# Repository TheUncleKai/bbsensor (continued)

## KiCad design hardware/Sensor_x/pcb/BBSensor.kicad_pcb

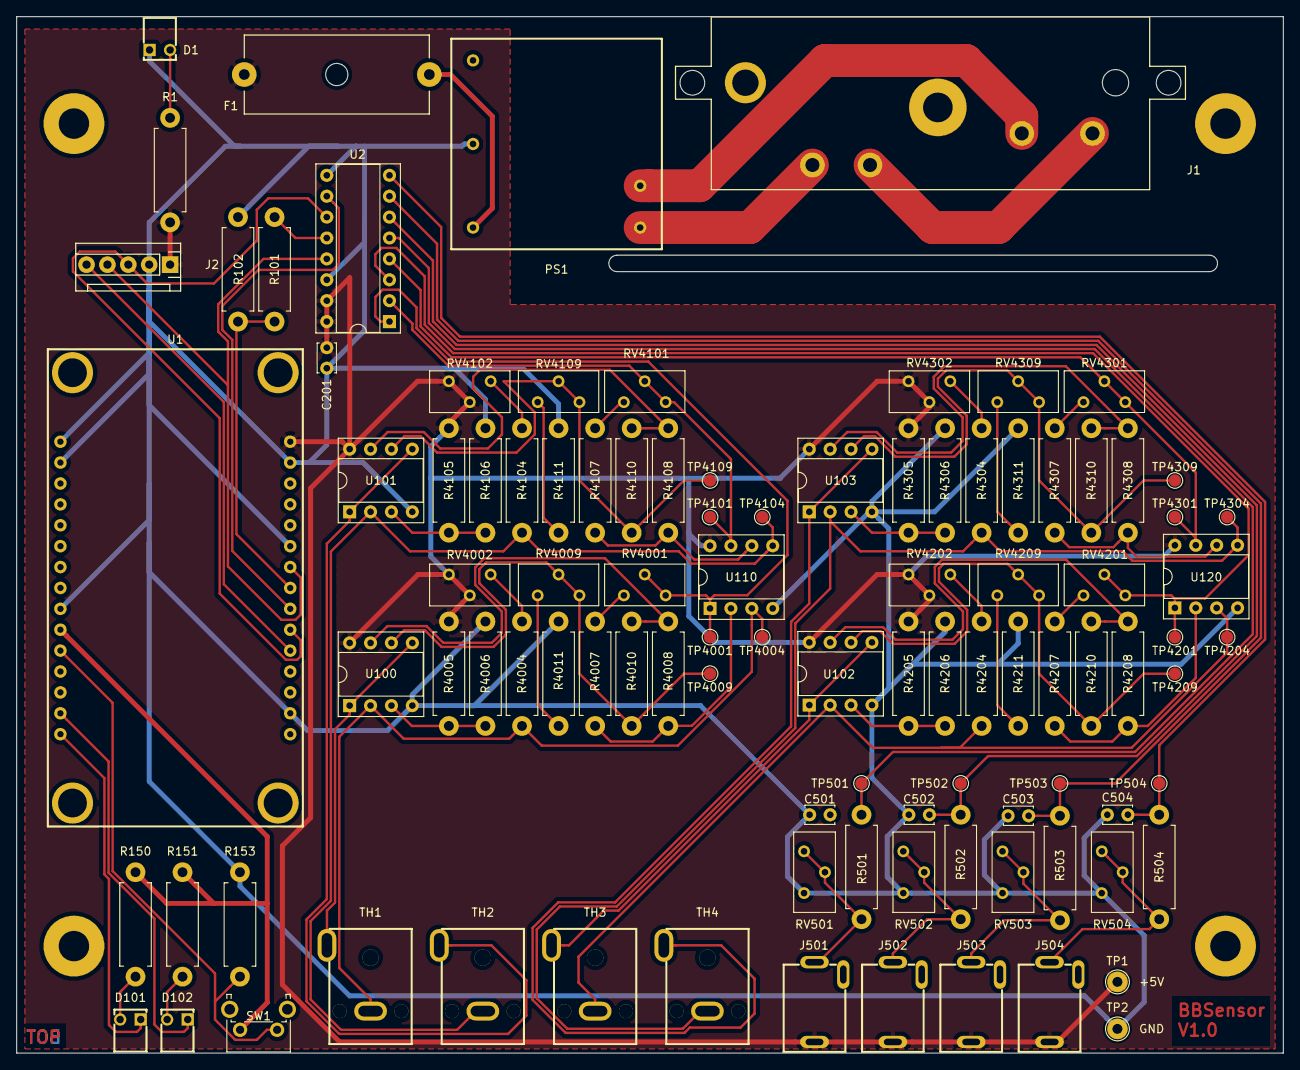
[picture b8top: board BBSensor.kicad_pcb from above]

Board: 2 copper layers, 154.0 x 126.0 mm, 101 parts (0 on the bottom side), 67 nets.

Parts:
C201, C501, C502, C503, C504: 100n; C_Disc_D3.4mm_W2.1mm_P2.50mm
D1: POWER; 5600F
D101: RED; 5600F
D102: GREEN; 5600F
F1: Fuse; Fuse_holder_20x5_22.5
J1: Schurter_CMF1; CMF1
J2: Display; Molex_KK256_Pin_Header_Straight_1x05
J501, J502, J503, J504: AudioJack2_SwitchT; LUMBERG_1501_09
PS1: TMPS_05; Traco_TMPS_05
R1: 220; R_Axial_DIN0411_L9.9mm_D3.6mm_P12.70mm_Horizontal
R101: 1k; R_Axial_DIN0411_L9.9mm_D3.6mm_P12.70mm_Horizontal
R102, R153, R4004, R4104, R4204, R4304: 2k2; R_Axial_DIN0411_L9.9mm_D3.6mm_P12.70mm_Horizontal
R150, R151: 140; R_Axial_DIN0411_L9.9mm_D3.6mm_P12.70mm_Horizontal
R501, R502, R503, R504, R4005, R4006, R4105, R4106, R4205, R4206, R4305, R4306: 10k; R_Axial_DIN0411_L9.9mm_D3.6mm_P12.70mm_Horizontal
R4007, R4107, R4207, R4307: 4k7; R_Axial_DIN0411_L9.9mm_D3.6mm_P12.70mm_Horizontal
R4008, R4010, R4108, R4110, R4208, R4210, R4308, R4310: 200; R_Axial_DIN0411_L9.9mm_D3.6mm_P12.70mm_Horizontal
R4011, R4111, R4211, R4311: 2k; R_Axial_DIN0411_L9.9mm_D3.6mm_P12.70mm_Horizontal
RV501, RV502, RV503, RV504: 10k; Potentiometer_Bourns_3296Y_Vertical
RV4001, RV4101, RV4201, RV4301: 405; Potentiometer_Bourns_3296Y_Vertical
RV4002, RV4102, RV4202, RV4302: 300; Potentiometer_Bourns_3296Y_Vertical
RV4009, RV4109, RV4209, RV4309: 470; Potentiometer_Bourns_3296Y_Vertical
SW1: SW_Push; SW_Tactile_SPST_Angled_PTS645Vx83-2LFS
TH1, TH2, TH3, TH4: Thermistor_NTC; LUMBERG_1553_02
TP1, TP2: TestPoint; TestPoint_THTPad_D2.5mm_Drill1.2mm
TP501, TP502, TP503, TP504, TP4001, TP4004, TP4009, TP4101, TP4104, TP4109, TP4201, TP4204, TP4209, TP4301, TP4304, TP4309: TestPoint; TestPoint_Pad_D1.5mm
U1: ESP8266-12E_NodeMCU_Lolin
U2: MCP3208; DIP-16_W7.62mm_Socket
U100, U101, U102, U103, U110, U120: OPA2340; DIP-8_W7.62mm_Socket

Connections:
+3V3: R150.1, R151.1, SW1.2, U1.21
+5V: C201.1, F1.1, J2.1, J501.S, J502.S, J503.S, J504.S, R1.2, R4005.2, R4105.2, R4205.2, R4305.2, RV4002.2, RV4002.3, RV4102.2, RV4102.3, RV4202.2, RV4202.3, RV4302.2, RV4302.3, TP1.1, U1.15, U2.15, U2.16, U100.8, U101.8, U102.8, U103.8, U110.8, U120.8
/Analog/Digital/SPI1: J2.3, U1.6, U2.11
/Analog/Digital/SPI2: R101.2, U2.12
/Analog/Digital/SPI3: J2.4, U1.9, U2.13
/Analog/Digital/SPI4: U1.7, U2.10
/Analog/Digital/TEMP1: RV4001.2, RV4001.3, TP4001.1, U2.1, U110.1
/Analog/Digital/TEMP2: RV4101.2, RV4101.3, TP4101.1, U2.2, U110.7
/Analog/Digital/TEMP3: RV4201.2, RV4201.3, TP4201.1, U2.3, U120.1
/Analog/Digital/TEMP4: RV4301.2, RV4301.3, TP4301.1, U2.4, U120.7
/Analog/Digital/TEMP5: C501.1, R501.1, TP501.1, U2.5
/Analog/Digital/TEMP6: C502.1, R502.1, TP502.1, U2.6
/Analog/Digital/TEMP7: C503.1, R503.1, TP503.1, U2.7
/Analog/Digital/TEMP8: C504.1, R504.1, TP504.1, U2.8
/Display/SPI5: J2.5, U1.5
/ESP8266/MISO: R101.1, R102.1, U1.8
GND: C201.2, C501.2, C502.2, C503.2, C504.2, D1.1, J2.2, PS1.4, R102.2, R153.2, R4006.1, R4011.2, R4106.1, R4111.2, R4206.1, R4211.2, R4306.1, R4311.2, RV501.3, RV502.3, RV503.3, RV504.3, TP2.1, U1.2, U1.10, U1.14, U1.22, U1.29, U1.30, U2.9, U2.14, U100.4, U101.4, U102.4, U103.4, U110.4, U120.4
unnamed: D1.2, R1.1
unnamed: D101.1, U1.16
unnamed: D101.2, R150.2
unnamed: D102.1, U1.17
unnamed: D102.2, R151.2
unnamed: F1.2, PS1.5
unnamed: J1.1, PS1.2
unnamed: J1.2, J1.4
unnamed: J1.3, PS1.1
unnamed: J501.T, R501.2, RV501.1, RV501.2
unnamed: J502.T, R502.2, RV502.1, RV502.2
unnamed: J503.T, R503.2, RV503.1, RV503.2
unnamed: J504.T, R504.2, RV504.1, RV504.2
unnamed: R153.1, SW1.1, U1.20
unnamed: R4004.1, TH1.2, TP4004.1, U100.2, U110.3
unnamed: R4004.2, RV4002.1
unnamed: R4005.1, R4006.2, U100.3
unnamed: R4007.1, RV4001.1
unnamed: R4007.2, R4008.1, U110.2
unnamed: R4008.2, R4010.1, U100.7
unnamed: R4010.2, RV4009.2, RV4009.3, TP4009.1, U100.6
unnamed: R4011.1, RV4009.1
unnamed: R4104.1, TH2.2, TP4104.1, U101.2, U110.5
unnamed: R4104.2, RV4102.1
unnamed: R4105.1, R4106.2, U101.3
unnamed: R4107.1, RV4101.1
unnamed: R4107.2, R4108.1, U110.6
unnamed: R4108.2, R4110.1, U101.7
unnamed: R4110.2, RV4109.2, RV4109.3, TP4109.1, U101.6
unnamed: R4111.1, RV4109.1
unnamed: R4204.1, TH3.2, TP4204.1, U102.2, U120.3
unnamed: R4204.2, RV4202.1
unnamed: R4205.1, R4206.2, U102.3
unnamed: R4207.1, RV4201.1
unnamed: R4207.2, R4208.1, U120.2
unnamed: R4208.2, R4210.1, U102.7
unnamed: R4210.2, RV4209.2, RV4209.3, TP4209.1, U102.6
unnamed: R4211.1, RV4209.1
unnamed: R4304.1, TH4.2, TP4304.1, U103.2, U120.5
unnamed: R4304.2, RV4302.1
unnamed: R4305.1, R4306.2, U103.3
unnamed: R4307.1, RV4301.1
unnamed: R4307.2, R4308.1, U120.6
unnamed: R4308.2, R4310.1, U103.7
unnamed: R4310.2, RV4309.2, RV4309.3, TP4309.1, U103.6
unnamed: R4311.1, RV4309.1
unnamed: TH1.1, U100.1, U100.5
unnamed: TH2.1, U101.1, U101.5
unnamed: TH3.1, U102.1, U102.5
unnamed: TH4.1, U103.1, U103.5

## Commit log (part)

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2019-08-28 feat: Create Scheme
    Add KiCad data
    Issue #1
2019-08-28 feat: Create Scheme
    add Temperatures
    Issue #1
2019-08-29 feat: Firmware: Create groundwork for the firmware
    add first test code and sketch
    Issue #3
2019-08-29 feat: Firmware: Create groundwork for the firmware
    move sketch file for arduino
    Issue #3
2019-08-29 feat: Project Managment
    add git commit messages
    Issue #8
2019-08-29 feat: Create Scheme
    redo voltage amps for Pt100 with Testpoints
    Issue #1
2019-08-30 feat: Create groundwork for the firmware
    prepare core
    Issue #3
2019-08-30 feat: Create groundwork for the firmware
    try to get Codeblocks working....
    Issue #3
2019-08-30 feat: Create groundwork for the firmware
    use correct files
    Issue #3
2019-08-30 feat: Create groundwork for the firmware
    prepare Core build lib
    Issue #3
2019-08-30 feat: Create groundwork for the firmware
    move files
    Issue #3
2019-08-31 feat: Create groundwork for the firmware
    fine tune rules
    Issue #3
2019-08-31 feat: Create groundwork for the firmware
    use cygwin make and tools as Makefile
    Issue #3
2019-08-31 feat: Create groundwork for the firmware
    add help for makefiles
    Issue #3
2019-09-01 feat: Create groundwork for the firmware
    show info
    Issue #3
2019-09-01 feat: Create groundwork for the firmware
    make upload work
    Issue #3
2019-09-01 feat: Firmware - Make basics work
    start for issue
    Issue #12
2019-09-02 feat: Split Display SPI converter from main PCB
    split display
    add new pcb
    Issue #13
2019-09-02 feat: Split Display SPI converter from main PCB
    small update
    Issue #13
2019-09-04 feat: General PCB improvements
    redo PCB, shrink it to 153 mm
    generate PCB VRML
    Issue #14
2019-09-05 feat: General PCB improvements
    switch Power inlet
    Issue #14
2019-09-08 feat: General PCB improvements
    add Pt100 CAD
    Issue #14
2019-09-09 feat: General PCB improvements
    rename to Pt100
    Issue #14
2019-09-09 feat: General PCB improvements
    add PTC sensor
    Issue #14
2019-09-09 feat: General PCB improvements
    redo PTC pcb
    Issue #14
2019-09-09 feat: General PCB improvements
    rename
    Issue #14
2019-09-09 feat: General PCB improvements
    add gerber and pdf files
    Issue #14
2019-09-09 feat: General PCB improvements
    add gerbv file
    Issue #14
2019-09-10 feat: General PCB improvements
    add Mini PCB (needs to be redone for RM2015L
    Issue #14
2019-09-11 feat: General PCB improvements
    finalize front, need to move mountings
    Issue #14
2019-09-13 feat: Add CAD for assembly
    add message for CAD
    Issue #16
2019-09-13 feat: Project Managment
    add some text
    Issue #8
2019-09-13 feat: Project Managment
    fix links again
    Issue #8
2019-09-16 feat: General PCB improvements
    redo BBMini
    Issue #14
2019-09-16 feat: General PCB improvements
    redo PTC
    Issue #14
2019-09-16 feat: General PCB improvements
    add BOM
    Issue #14
2019-09-17 feat: Add CAD for assembly
    add PCB screws
    Issue #16
2019-09-18 feat: Firmware - Make basics work
    implement LED class, make LED blink working
    Issue #12
2019-09-18 feat: Firmware - Make basics work
    rename sensor to main
    Issue #12
2019-09-18 feat: Firmware - Make basics work
    change rights
    Issue #12
2019-09-19 feat: Firmware - Make basics work
    redo dependency handling
    Issue #12
2019-09-19 feat: Firmware - Make basics work
    finalize core compile
    Issue #12
2019-09-19 feat: Firmware - Make basics work
    add .cpp/.S stuff
    Issue #12
2019-09-19 feat: Firmware - Make basics work
    add SPI
    Issue #12
2019-09-20 feat: Firmware - Make basics work
    switch PINs for SPI Interface
    Issue #12
2019-09-20 feat: Firmware - Make basics work
    count loops
    Issue #12
2019-09-20 feat: Firmware - Make basics work
    reomove layout files for Code::Blokcs
    Issue #12
2019-09-20 feat: Firmware - Make basics work
    add button class
    Issue #12
2019-09-20 feat: Firmware - Make basics work
    * add license header
    Issue #12
2019-09-22 feat: Firmware - Make basics work
    add debug, try to get double working
    Issue #12
2019-09-23 feat: Firmware - Make basics work
    add second push button
    Issue #12
2019-09-23 feat: Firmware - Make basics work
    * prepare display and temperature
    Issue #12
2019-09-23 feat: Firmware - Make basics work
    * add EEPROM
    Issue #12
2019-09-23 feat: Firmware - Make basics work
    * move flag include
    Issue #12
2019-09-23 feat: Firmware - Make basics work
    * redo lib Makefiles
    Issue #12
2019-09-23 feat: Firmware - Make basics work
    * add more libs
    Issue #12
2019-09-23 feat: Firmware - Make basics work
    * add search folders
    Issue #12
2019-09-24 feat: BBMini2 - experimental ESP8266 PCB (SMD)
    * prepare message
    Issue #23
2019-09-25 feat: BBMini2 - experimental ESP8266 PCB (SMD)
    * update pcb
    Issue #23
2019-09-26 feat: BBMini2 - experimental ESP8266 PCB (SMD)
    * shrink PCB, switch components
    Issue #23
2019-09-27 feat: BBMini2 - experimental ESP8266 PCB (SMD)
    * add nee stuff
    Issue #23
2019-09-28 feat: Firmware: Add Display
    * use correct buttons and LED PINs in PCB
    Issue #5
2019-09-29 feat: Firmware: Add Display
    * make SPI work, need to reroute CS Pins
    Issue #5
2019-09-29 feat: Firmware: Add Display
    * cleanup transfer code, convert to device code as extra SPI
    Issue #5
2019-09-30 feat: BBMini2 - experimental ESP8266 PCB (SMD)
    * update Mini2 with current SDK
    Issue #23
2019-10-01 feat: BBMini2 - experimental ESP8266 PCB (SMD)
    * redo PCB, add CAD
    * make space for Display
    Issue #23
2019-10-05 feat: Firmware: Add Display
    * set two pins on
    Issue #5
2019-10-06 feat: Firmware: Add Display
    * redo debug output for SPI
    Issue #5
2019-10-06 feat: Firmware: Add Display
    * add pin converter for Display
    Issue #5
2019-10-09 feat: BBMini2 - experimental ESP8266 PCB (SMD)
    * redo case for new Mini2
    Issue #23
2019-10-10 feat: BBMini2 - experimental ESP8266 PCB (SMD)
    * implement Case, add 9 V block holder
    Issue #23
2019-10-14 feat: Version 3: Experimental PCB with only one ADC and multiplexer
    prepare single ADC version
    Issue #24
2019-10-15 feat: Version 3: Experimental PCB with only one ADC and multiplexer
    implemenrt multiplexer
    Issue #24
2019-10-16 feat: Version 3: Experimental PCB with only one ADC and multiplexer
    shrink stuff, start pcb
    Issue #24
2019-10-27 feat: Firmware: Add Display
    fix signals, make display work
    Issue #5
2019-10-27 feat: Firmware: Add Display
    Display is done
    Issue #5
2019-10-29 feat: Firmware: Add Display
    cleanup debug settings
    Issue #5
2019-11-03 feat: Firmware: Read temperatures
    start reading of Temperatures
    Issue #4
2019-11-04 feat: Firmware: Read temperatures
    redo SPI handling via lists and parse results
    Issue #4
2019-11-05 feat: Firmware: Read temperatures
    siwtch from int and byte to uint8_t/uint16_t
    Issue #4
2019-11-10 admin: Project Managment
    redo messages
    Issue #8
2019-11-16 feat: Firmware: Convert Temperatures
    prepare add tables with temperatures
    add sheet with voltages
    read two temps from main
    Issue #27
2019-11-16 feat: Firmware: Convert Temperatures
    convert to voltage
    Issue #27
2019-11-17 feat: Firmware: Read Config from EEPROM
    read and store config
    Issue #28
2019-11-20 feat: Firmware: Convert Temperatures
    simplyfy config
    Issue #27
2019-11-20 feat: Firmware: Switch to ESP8266 2.6.1 SDK
    add ld file to repo
    Issue #33
2019-11-23 feat: Firmware: Read Config from EEPROM
    add auto expanding dependency list for build system
    Issue #28
2019-11-23 feat: Firmware: Read Config from EEPROM
    add ext for CRC32
    Issue #28
2019-11-23 feat: Firmware: Read Config from EEPROM
    read CRC from EEPROM
    Issue #28
2019-11-24 feat: Firmware: Read Config from EEPROM
    cleanup defines
    Issue #28
2019-11-24 feat: Firmware: Read Config from EEPROM
    replace std with low level stuff
    Issue #28
2019-11-24 feat: Firmware: Read Config from EEPROM
    tune main
    Issue #28
2019-11-24 feat: Firmware: Read Config from EEPROM
    finish config
    Issue #28
2019-11-24 feat Firmware: Convert Temperatures
    replace string
    Issue #27
2019-11-25 feat: Firmware: Convert Temperatures
    implement release flag
    Issue #27
2019-11-25 feat: Firmware: Convert Temperatures
    cleanup and simplify
    Issue #27
2019-11-27 feat: Firmware: Convert Temperatures
    remove toggle from main, move to temperature
    Issue #27
2019-11-28 feat: Firmware: Code seperation into own lib
    rename src to app
    Issue #37
2019-11-28 feat: Firmware: Code seperation into own lib
    move sketch
    Issue #37
2019-11-28 feat: Firmware: Code seperation into own lib
    make makefile work
    Issue #37
2019-11-28 feat: Firmware: Convert Temperatures
    remove utils
    fix missing ptc100
    switch to heap for cannels again
    Issue #27
2019-12-01 feat: Firmware: Use ESP32 Module
    Add Board docs for ESP32
    Issue #37
2019-12-01 feat: Firmware: Use ESP32 Module
    reorganize structure
    Issue #37
2019-12-01 feat: Firmware: Use ESP32 Module
    finish ESP8266
    Issue #37
2019-12-01 feat: Firmware: Use ESP32 Module
    remove crap
    Issue #37
2019-12-01 feat: Firmware: Use ESP32 Module
    remove debug
    Issue #37
2019-12-01 feat: Firmware: Use ESP32 Module
    add templates
    Issue #37
2019-12-01 feat Firmware: Convert Temperatures
    purge debug.h
    Issue #27
2019-12-01 feat Firmware: Convert Temperatures
    reenable stuff
    Issue #27
2019-12-01 feat: Firmware: Use ESP32 Module
    add flags for upload
    Issue #38
2019-12-01 feat: Firmware: Use ESP32 Module
    fix debug in lib
    Issue #38
2019-12-01 feat: Firmware: Use ESP32 Module
    add docs
    Issue #38
2019-12-01 feat Firmware: Convert Temperatures
    better toggle
    Issue #27
2019-12-01 feat Firmware: Convert Temperatures
    simplify toggle
    Issue #27
2019-12-02 feat: Firmware: Convert Temperatures
    cleanup and better output
    Issue #27
2019-12-03 feat: Hardware: Use ESP32 Module
    use ESP32 in BBSensor
    Issue #41
2019-12-08 feat: Firmware: Use ESP32 Module
    finish conversion to ESP32
    Issue #38
2019-12-10 remove stuff
2019-12-11 feat: Firmware: Convert Temperatures
    reduce code overhead
    Issue #27
2019-12-16 feat: Hardware: Use ESP32 Module
    redo Mini32 PCB
    Issue #41
2019-12-17 feat: Hardware: Use ESP32 Module
    add new ESP32 module
    Issue #41
2019-12-23 feat: Hardware: Use ESP32 Module
    shrink board with SMD
    Issue #41
2019-12-23 feat Firmware: Convert Temperatures
    fix button click
    Issue #27
2019-12-23 feat: Replace Hardware class
    simplify hardware class
    Issue #45
2019-12-24 feat Firmware: Convert Temperatures
    tweaks for measurement, add first log with results
    Issue #27
2019-12-25 feat: Hardware: Use ESP32 Module
    add Calibration matrix
    Issue #41
2020-02-17 feat: Use NPN to control display
    add NPN and code
    Issue #47
2020-02-19 feat: Split 5V rail from main PCB
    split 5 V from PCB, remove old stuff
    Issue #51
2020-02-20 feat: Split +5V rail from PCB
    redo normal PCB
    Issue #51
2020-02-21 feat: Use transistor to control display
    redo
    Issue #47
2020-02-22 feat: Split 5V rail from main PCB
    redo PCB, start lid
    Issue #51
2020-02-23 feat: Firmware: Convert Temperatures
    redo PCB with new Transistors
    Issue #27
2020-02-25 feat: Use transistor to control display
    reinsert 5V rail
    Issue #47
2020-02-26 feat: Firmware: Convert Temperatures
    finalize case design
    Issue #27
2020-02-27 feat: Firmware: Convert Temperatures
    redo FreeCAD
    Issue #27
2020-02-28 feat: Firmware: Convert Temperatures
    add first prototype of case
    Issue #27
